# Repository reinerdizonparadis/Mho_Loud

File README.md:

# Mho Loud - Engineering Electronics I Laboratory Final Project

UNLV College of Engineering - Department of Electrical & Computer Engineering<br>
**Class**: EE 320L<br>
**Author**: Reiner Dizon<br><br>

Schematic and PCB are included. Refer to Project Report PDF for more details.

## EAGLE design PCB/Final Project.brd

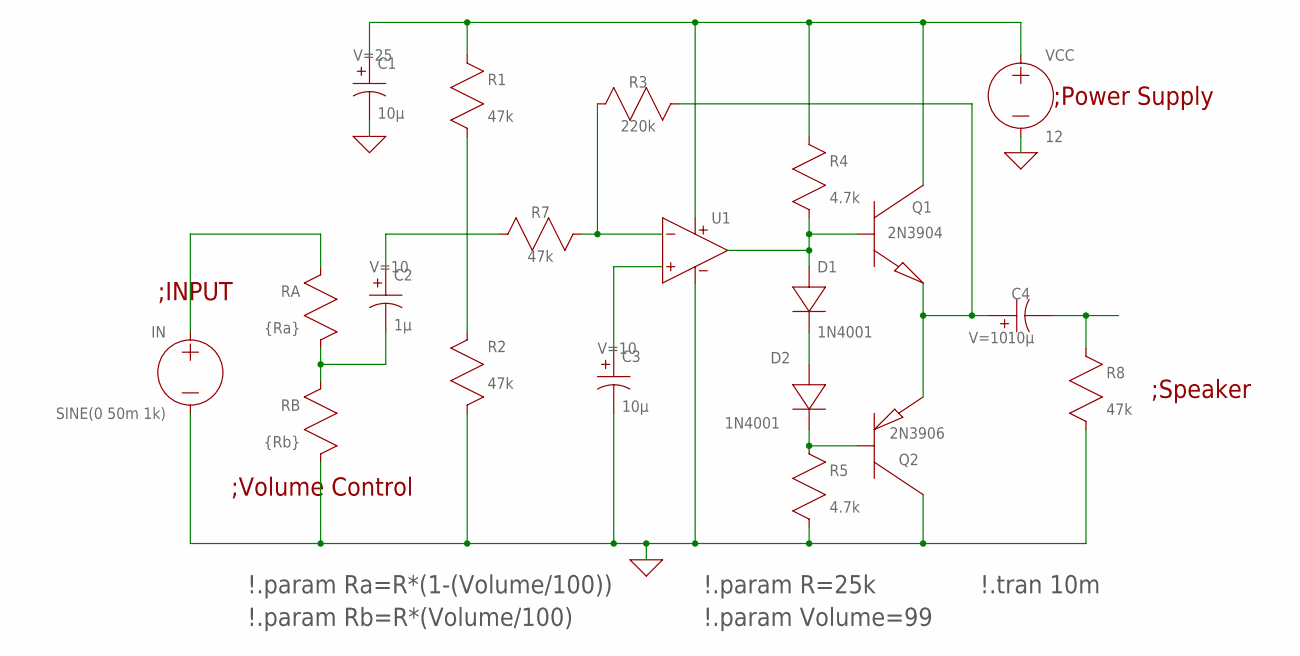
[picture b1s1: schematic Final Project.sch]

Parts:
C1, C3, C4: 10µ; PANASONIC_D
C2: 1µ; PANASONIC_D
D1, D2: 1N4001; SOD123
Q1: 2N3904; SOT23
Q2: 2N3906; SOT23
R1, R2, R7, R8: 47k; R0805
R3: 220k; R0805
R4, R5: 4.7k; R0805
RA: {Ra}; R0805
RB: {Rb}; R0805
U1: UNIVERSALOPAMP2; S8

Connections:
0: C1.- (B), C3.- (B), Q2.3 (C), R2.1 (A), R5.2 (B), R8.2 (B), RB.2 (B), U1.4 (V-)
unnamed: C1.+ (A), Q1.3 (C), R1.1 (A), R4.1 (A), U1.8 (V+)
unnamed: C4.+ (A), Q1.1 (E), Q2.1 (E), R3.2 (B)
unnamed: C2.+ (A), R7.2 (B)
unnamed: R3.1 (A), R7.1 (A), U1.2 (IN-)
unnamed: D1.A (+), Q1.2 (B), R4.2 (B), U1.3 (OUT)
unnamed: C3.+ (A), U1.1 (IN+)
unnamed: C4.- (B), R8.1 (A)
unnamed: R1.2 (B), R2.2 (B)
unnamed: C2.- (B), RA.2 (B), RB.1 (A)
unnamed: D1.C (-), D2.A (+)
unnamed: D2.C (-), Q2.2 (B), R5.1 (A)

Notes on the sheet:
;Volume Control
;Speaker
;Power Supply
\!.param Rb=R*(Volume/100)
\!.param Ra=R*(1-(Volume/100))
\!.tran 10m
\!.param R=25k
\!.param Volume=99
;INPUT

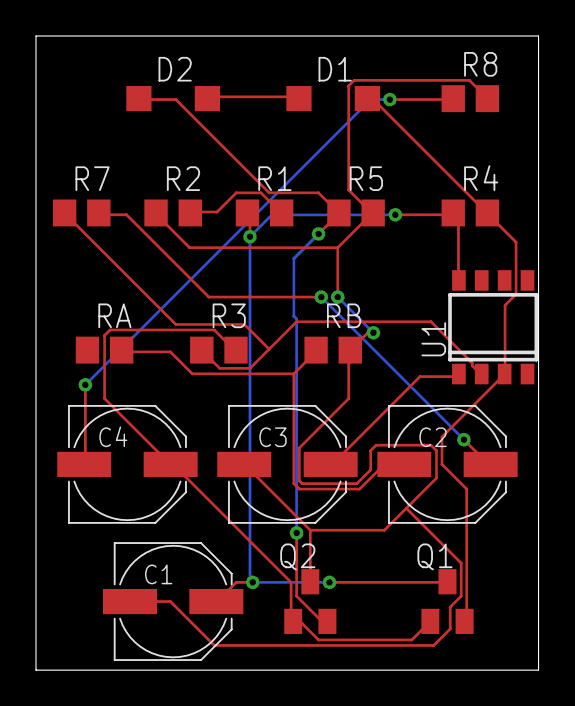
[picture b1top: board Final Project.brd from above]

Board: 2 copper layers, 27.9 x 35.2 mm, 18 parts (0 on the bottom side), 12 nets.
